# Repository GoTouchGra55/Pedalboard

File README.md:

# Multi-Effects Pedal Board

A custom multi-effects guitar pedal board combining several audio effects into one compact unit. Designed primarily as a learning project to explore analog audio circuits, signal processing, and embedded control systems (obv).

Also I needed effects pedals and those things are absurdly expensive ;')

---

## Features

- **Distortion & Overdrive** – From mild warmth to heavy saturation
- **Chorus** – Thickens and widens the sound
- **Tremolo** – Rhythmic volume modulation
- **Delay** – Adds echo and spatial depth

---

##  Signal Chain

Input -> Overdrive/Distortion -> Chorus -> Tremolo -> Delay -> Output

> _Note: Signal order can be adjusted depending on design preferences._

---

## Power Requirements

- **Input Voltage:** 9V DC (center-negative)
- **Power Supply:** Regulated recommended
- Includes onboard regulation and decoupling for noise reduction

---

## Hardware Overview

- Individual circuits for each effect
- Decoupling capacitors for stable operation

---

## I/O

- **Input Jack:** 1/4" mono
- **Output Jack:** 1/4" mono
- **DC Jack:** 9V input

---

## 3D View

---

## Routing

## BOM

| Component | Purpose | Qty | Total Cost (USD) | Distributor |
|---|---|---:|---:|---|
| Stomp Switch | Toggle each effect | 1 | 25.53 | Daraz Nepal |
| 50k Potentiometer | Used in circuit | 1 | 7.38 | Daraz Nepal |
| 20k Potentiometer | Used in circuit | 1 | 5.08 | Daraz Nepal |
| 2k Potentiometer | Used in circuit | 1 | 5.22 | Daraz Nepal |
| 10k Potentiometer | Used in circuit | 1 | 0.63 | Daraz Nepal |
| 100k Potentiometer | Used in circuit | 1 | 1.24 | Daraz Nepal |
| 500k Potentiometer | Used in circuit | 1 | 5.08 | Daraz Nepal |
| B100k Potentiometer | Used in circuit | 1 | 0.50 | Daraz Nepal |
| B500K Potentiometer | Used in circuit | 1 | 0.50 | Daraz Nepal |
| PCB | Houses all components | 1 | 8.20 | JLCPCB |
| DC Barrel Jack | Power input connector | 1 | 0.44 | Daraz Nepal |
| 1uF Capacitor | Charge storage/filtering | 1 | 0.88 | Daraz Nepal |
| 220nF Capacitor | Charge storage/filtering | 1 | 0.88 | Daraz Nepal |
| 100nF Capacitor | Charge storage/filtering | 1 | 1.82 | Daraz Nepal |
| Ceramic Capacitors Kit | Misc capacitor assortment | 1 | 7.91 | Daraz Nepal |
| Capacitor Kit | General purpose capacitors | 1 | 2.97 | Daraz Nepal |
| 2.2M Resistor | Current limiting | 1 | 0.66 | Daraz Nepal |
| Resistor Kit | General purpose resistors | 1 | 3.92 | Daraz Nepal |
| LDR | Tremolo light-dependent resistance | 1 | 2.27 | Daraz Nepal |
| LED | Status indication | 1 | 0.87 | Daraz Nepal |
| Voltage Regulator (7805) | Voltage regulation | 1 | 1.31 | Daraz Nepal |
| PT2399 IC | Delay/chorus processing IC | 1 | 2.36 | Daraz Nepal |
| LM555 Timer | PWM generation for tremolo | 1 | 2.00 | Daraz Nepal |
| NE5532 Op Amp | Chorus effect op amp | 1 | 1.78 | Daraz Nepal |
| TL072 | Gain/effects op amp | 1 | 1.69 | Daraz Nepal |
| Diode | One-way current flow | 1 | 0.40 | Daraz Nepal |
| Schottky Diode | Fast low-drop diode | 1 | 0.93 | Daraz Nepal |
| 1N4148 Diode | Signal diode | 1 | 0.27 | Daraz Nepal |
| 2N3904 Transistor | Signal filtering/amplification | 1 | 0.63 | Daraz Nepal |
| Guitar Jack Socket | Guitar/amp I/O connection | 2 | 2.07 | Daraz Nepal |

## Estimated Total Cost

**~$94.54 USD**

> Note: Prices may vary depending on shipping, stock availability, and quantity ordered.

---

## Suppliers

- Daraz Nepal
- JLCPCB

---

## Notes

- Passive component kits (capacitors/resistors) include multiple values and quantities.
- Potentiometer values may vary depending on the final pedal circuit tuning.
- PCB pricing is estimated from JLCPCB prototype manufacturing quotes.

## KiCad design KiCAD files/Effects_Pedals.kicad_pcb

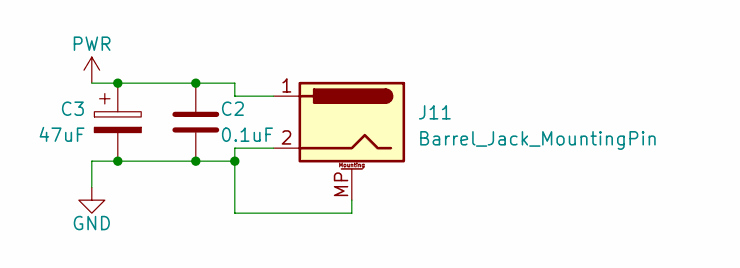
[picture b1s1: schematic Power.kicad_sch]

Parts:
C2: 0.1uF; C_Disc_D3.0mm_W2.0mm_P2.50mm
C3: 47uF; CP_Radial_D4.0mm_P1.50mm
J11: Barrel_Jack_MountingPin; BarrelJack_Horizontal

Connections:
GND: C2.2, C3.2, J11.2, J11.MP (MountPin); also elsewhere on the board
PWR: C2.1, C3.1, J11.1; also elsewhere on the board

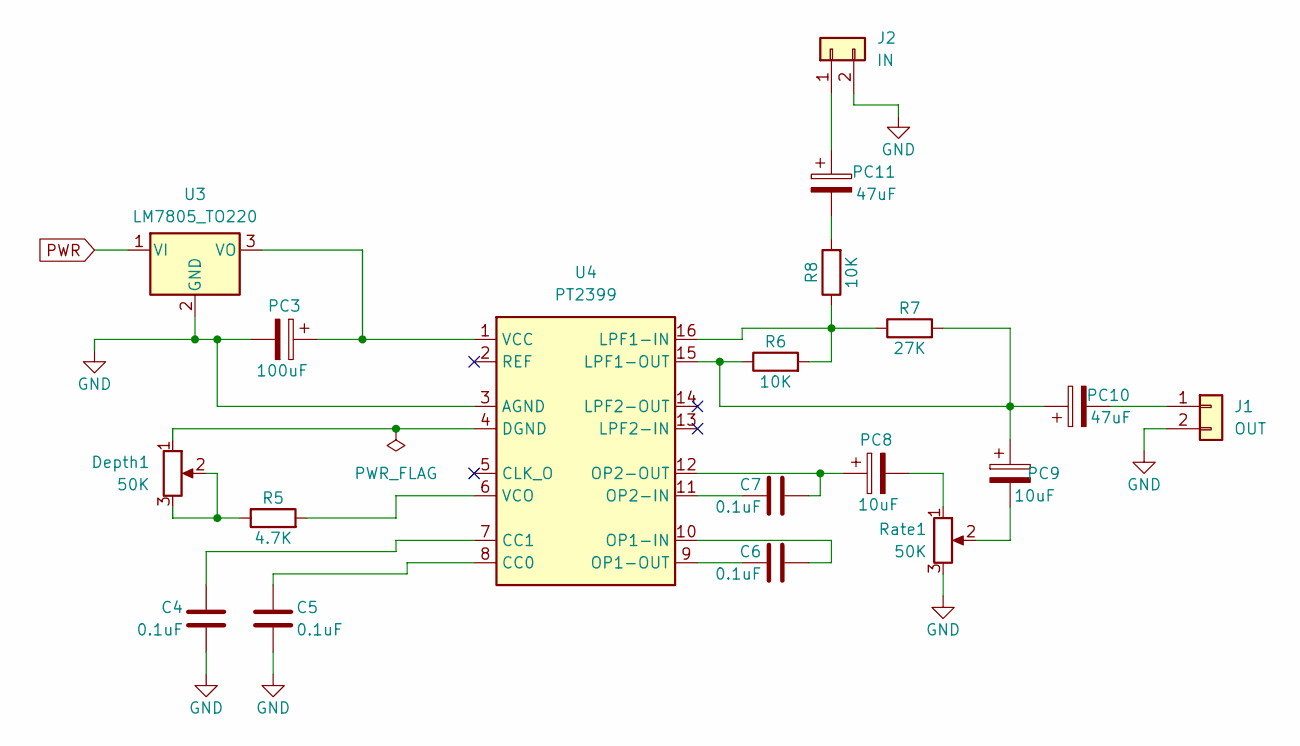
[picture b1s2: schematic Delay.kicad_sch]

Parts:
C4, C5, C6, C7: 0.1uF; C_Disc_D3.0mm_W2.0mm_P2.50mm
Depth1: 50K; PinSocket_1x03_P2.54mm_Vertical
J1: OUT; PinHeader_1x02_P1.00mm_Vertical
J2: IN; PinHeader_1x02_P1.00mm_Vertical
PC3: 100uF; CP_Radial_D4.0mm_P1.50mm
PC8, PC9: 10uF; CP_Radial_D4.0mm_P1.50mm
PC10, PC11: 47uF; CP_Radial_D4.0mm_P1.50mm
R5: 4.7K; R_Axial_DIN0207_L6.3mm_D2.5mm_P7.62mm_Horizontal
R6, R8: 10K; R_Axial_DIN0207_L6.3mm_D2.5mm_P7.62mm_Horizontal
R7: 27K; R_Axial_DIN0207_L6.3mm_D2.5mm_P7.62mm_Horizontal
Rate1: 50K; PinSocket_1x03_P2.54mm_Vertical
U3: LM7805_TO220; TO-220-3_Vertical
U4: PT2399; DIP-16_W7.62mm

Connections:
GND: C4.2, C5.2, J1.2, J2.2, PC3.2, Rate1.3, U3.2 (GND), U4.3 (AGND); also elsewhere on the board
unnamed: Depth1.2, Depth1.3, R5.1
unnamed: J1.1, PC10.2
unnamed: J2.1, PC11.1
unnamed: PC8.2, Rate1.1
unnamed: PC9.2, Rate1.2
unnamed: PC11.2, R8.2
unnamed: PC3.1, U3.3 (VO), U4.1 (VCC)
unnamed: C5.1, U4.8 (CC0)
unnamed: C4.1, U4.7 (CC1)
unnamed: Depth1.1, U4.4 (DGND)
unnamed: R6.2, R7.1, R8.1, U4.16 (LPF1-IN)
unnamed: PC9.1, PC10.1, R6.1, R7.2, U4.15 (LPF1-OUT)
unnamed: C6.2, U4.10 (OP1-IN)
unnamed: C6.1, U4.9 (OP1-OUT)
unnamed: C7.1, U4.11 (OP2-IN)
unnamed: C7.2, PC8.1, U4.12 (OP2-OUT)
unnamed: R5.2, U4.6 (VCO)
PWR: U3.1 (VI); also elsewhere on the board

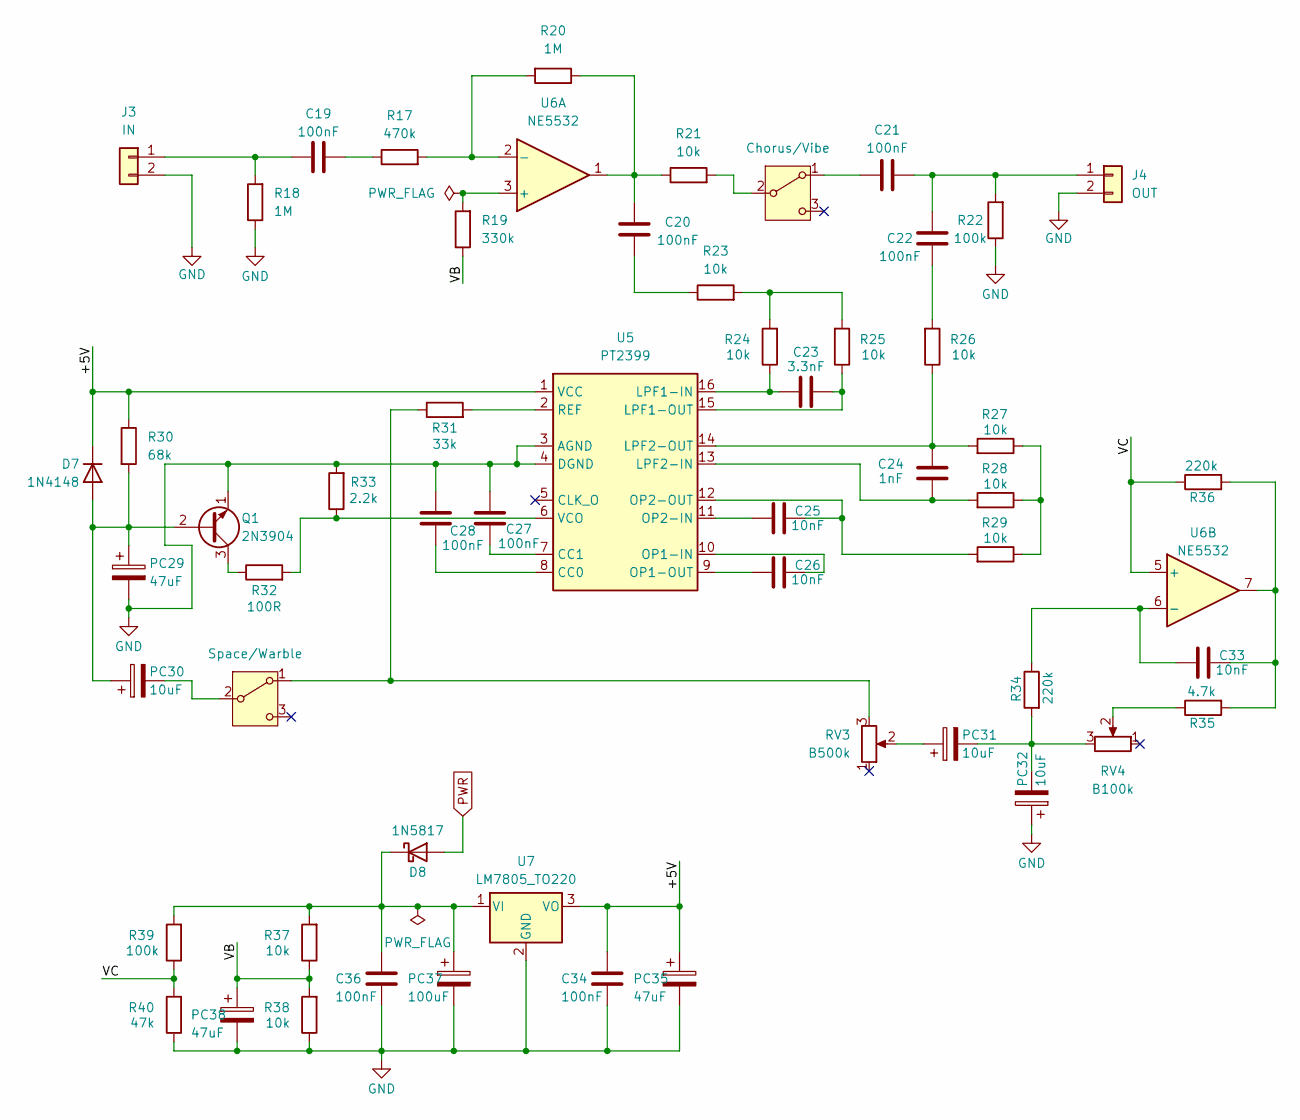
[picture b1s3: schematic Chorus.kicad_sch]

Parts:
C19, C20, C21, C22, C27, C28, C34, C36: 100nF; C_Disc_D3.0mm_W2.0mm_P2.50mm
C23: 3.3nF; C_Disc_D3.0mm_W2.0mm_P2.50mm
C24: 1nF; C_Disc_D3.0mm_W2.0mm_P2.50mm
C25, C26, C33: 10nF; C_Disc_D3.0mm_W2.0mm_P2.50mm
D7: 1N4148; D_DO-35_SOD27_P7.62mm_Horizontal
D8: 1N5817; D_DO-41_SOD81_P10.16mm_Horizontal
J3: IN; PinHeader_1x02_P1.00mm_Vertical
J4: OUT; PinHeader_1x02_P1.00mm_Vertical
PC29, PC35, PC38: 47uF; CP_Radial_D4.0mm_P1.50mm
PC30, PC31, PC32: 10uF; CP_Radial_D4.0mm_P1.50mm
PC37: 100uF; CP_Radial_D4.0mm_P1.50mm
Q1: 2N3904; TO-92_Inline
R17: 470k; R_Axial_DIN0207_L6.3mm_D2.5mm_P7.62mm_Horizontal
R18, R20: 1M; R_Axial_DIN0207_L6.3mm_D2.5mm_P7.62mm_Horizontal
R19: 330k; R_Axial_DIN0207_L6.3mm_D2.5mm_P7.62mm_Horizontal
R21, R23, R24, R25, R26, R27, R28, R29, R37, R38: 10k; R_Axial_DIN0207_L6.3mm_D2.5mm_P7.62mm_Horizontal
R22, R39: 100k; R_Axial_DIN0207_L6.3mm_D2.5mm_P7.62mm_Horizontal
R30: 68k; R_Axial_DIN0207_L6.3mm_D2.5mm_P7.62mm_Horizontal
R31: 33k; R_Axial_DIN0207_L6.3mm_D2.5mm_P7.62mm_Horizontal
R32: 100R; R_Axial_DIN0207_L6.3mm_D2.5mm_P7.62mm_Horizontal
R33: 2.2k; R_Axial_DIN0207_L6.3mm_D2.5mm_P7.62mm_Horizontal
R34, R36: 220k; R_Axial_DIN0207_L6.3mm_D2.5mm_P7.62mm_Horizontal
R35: 4.7k; R_Axial_DIN0207_L6.3mm_D2.5mm_P7.62mm_Horizontal
R40: 47k; R_Axial_DIN0207_L6.3mm_D2.5mm_P7.62mm_Horizontal
RV3: B500k; PinSocket_1x03_P2.54mm_Vertical
RV4: B100k; PinSocket_1x03_P2.54mm_Vertical
SW1: Chorus/Vibe; PinSocket_1x03_P2.54mm_Vertical
SW3: Space/Warble; PinSocket_1x03_P2.54mm_Vertical
U5: PT2399; DIP-16_W7.62mm
U6: NE5532; DIP-8_W7.62mm
U7: LM7805_TO220; TO-220-3_Vertical

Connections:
/Chorus/+5V: C34.1, D7.1 (K), PC35.1, R30.1, U5.1 (VCC), U7.3 (VO)
/Chorus/VB: PC38.1, R19.1, R37.1, R38.2
/Chorus/VC: R36.1, R39.1, R40.2, U6.5 (+)
GND: C27.1, C28.1, C34.2, C36.2, J3.2, J4.2, PC29.2, PC32.1, PC35.2, PC37.2, PC38.2, Q1.1 (E), R18.1, R22.1, R33.2, R38.1, R40.1, U5.3 (AGND), U5.4 (DGND), U7.2 (GND); also elsewhere on the board
unnamed: C19.2, R17.1
unnamed: C20.1, R23.1
unnamed: C20.2, R20.1, R21.1, U6.1
unnamed: C22.2, R26.2
unnamed: C33.1, R35.2, R36.2, U6.7
unnamed: D7.2 (A), PC29.1, PC30.1, Q1.2 (B), R30.2
unnamed: C36.1, D8.1 (K), PC37.1, R37.2, R39.2, U7.1 (VI)
unnamed: C19.1, J3.1, R18.2
unnamed: C21.1, C22.1, J4.1, R22.2
unnamed: PC31.1, RV3.2
unnamed: PC31.2, PC32.2, R34.2, RV4.3
unnamed: Q1.3 (C), R32.1
unnamed: R23.2, R24.2, R25.2
unnamed: R27.1, R28.1, R29.1
unnamed: R35.1, RV4.2
unnamed: C21.2, SW1.1 (A)
unnamed: R21.2, SW1.2 (B)
unnamed: R31.1, RV3.3, SW3.1 (A)
unnamed: PC30.2, SW3.2 (B)
unnamed: C28.2, U5.8 (CC0)
unnamed: C27.2, U5.7 (CC1)
unnamed: C23.2, R24.1, U5.16 (LPF1-IN)
unnamed: C23.1, R25.1, U5.15 (LPF1-OUT)
unnamed: C24.2, R28.2, U5.13 (LPF2-IN)
unnamed: C24.1, R26.1, R27.2, U5.14 (LPF2-OUT)
unnamed: C26.1, U5.10 (OP1-IN)
unnamed: C26.2, U5.9 (OP1-OUT)
unnamed: C25.2, U5.11 (OP2-IN)
unnamed: C25.1, R29.2, U5.12 (OP2-OUT)
unnamed: R31.2, U5.2 (REF)
unnamed: R32.2, R33.1, U5.6 (VCO)
unnamed: R19.2, U6.3 (+)
unnamed: R17.2, R20.2, U6.2 (-)
unnamed: C33.2, R34.1, U6.6 (-)
PWR: D8.2 (A); also elsewhere on the board

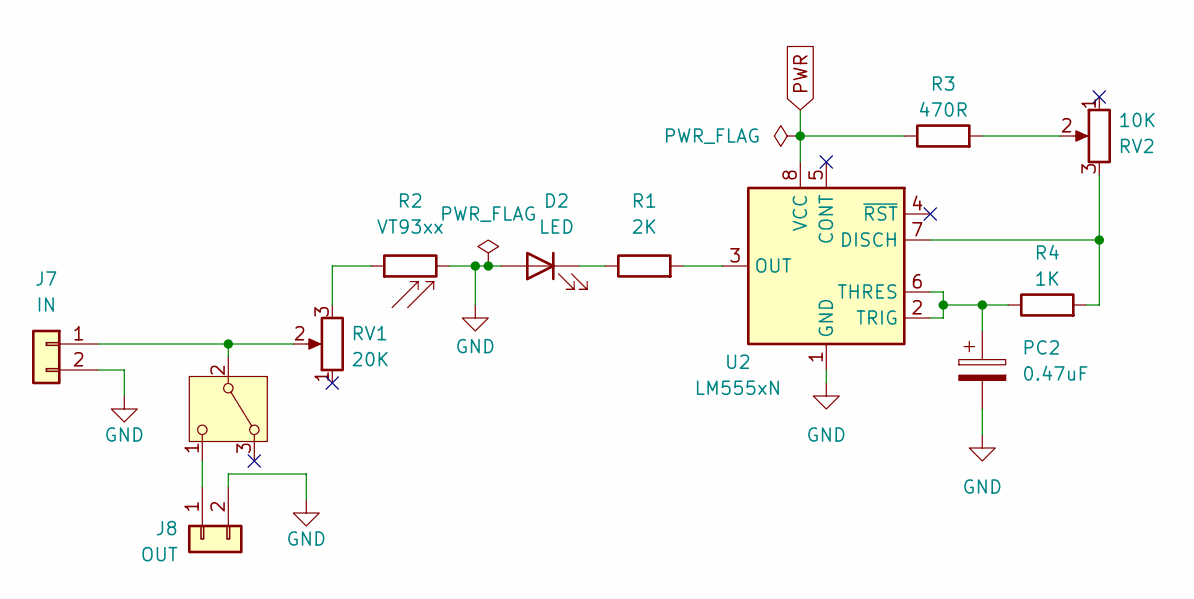
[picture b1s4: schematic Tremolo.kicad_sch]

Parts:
D2: LED; LED_D5.0mm
J7: IN; PinHeader_1x02_P1.00mm_Vertical
J8: OUT; PinHeader_1x02_P1.00mm_Vertical
PC2: 0.47uF; CP_Radial_D4.0mm_P1.50mm
R1: 2K; R_Axial_DIN0207_L6.3mm_D2.5mm_P7.62mm_Horizontal
R2: VT93xx; R_LDR_4.9x4.2mm_P2.54mm_Vertical
R3: 470R; R_Axial_DIN0207_L6.3mm_D2.5mm_P7.62mm_Horizontal
R4: 1K; R_Axial_DIN0207_L6.3mm_D2.5mm_P7.62mm_Horizontal
RV1: 20K; PinSocket_1x03_P2.54mm_Vertical
RV2: 10K; PinSocket_1x03_P2.54mm_Vertical
SW2: SW_Nidec_CAS-120A1; PinSocket_1x02_P2.54mm_Vertical
U2: LM555xN; DIP-8_W7.62mm

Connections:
GND: D2.2 (A), J7.2, J8.2, PC2.2, R2.2, U2.1 (GND); also elsewhere on the board
unnamed: D2.1 (K), R1.1
unnamed: J7.1, RV1.2, SW2.2 (B)
unnamed: J8.1, SW2.1 (C)
unnamed: R2.1, RV1.3
unnamed: R3.2, RV2.2
unnamed: R4.2, RV2.3, U2.7 (DISCH)
unnamed: R1.2, U2.3 (OUT)
unnamed: PC2.1, R4.1, U2.2 (TRIG), U2.6 (THRES)
PWR: R3.1, U2.8 (VCC); also elsewhere on the board

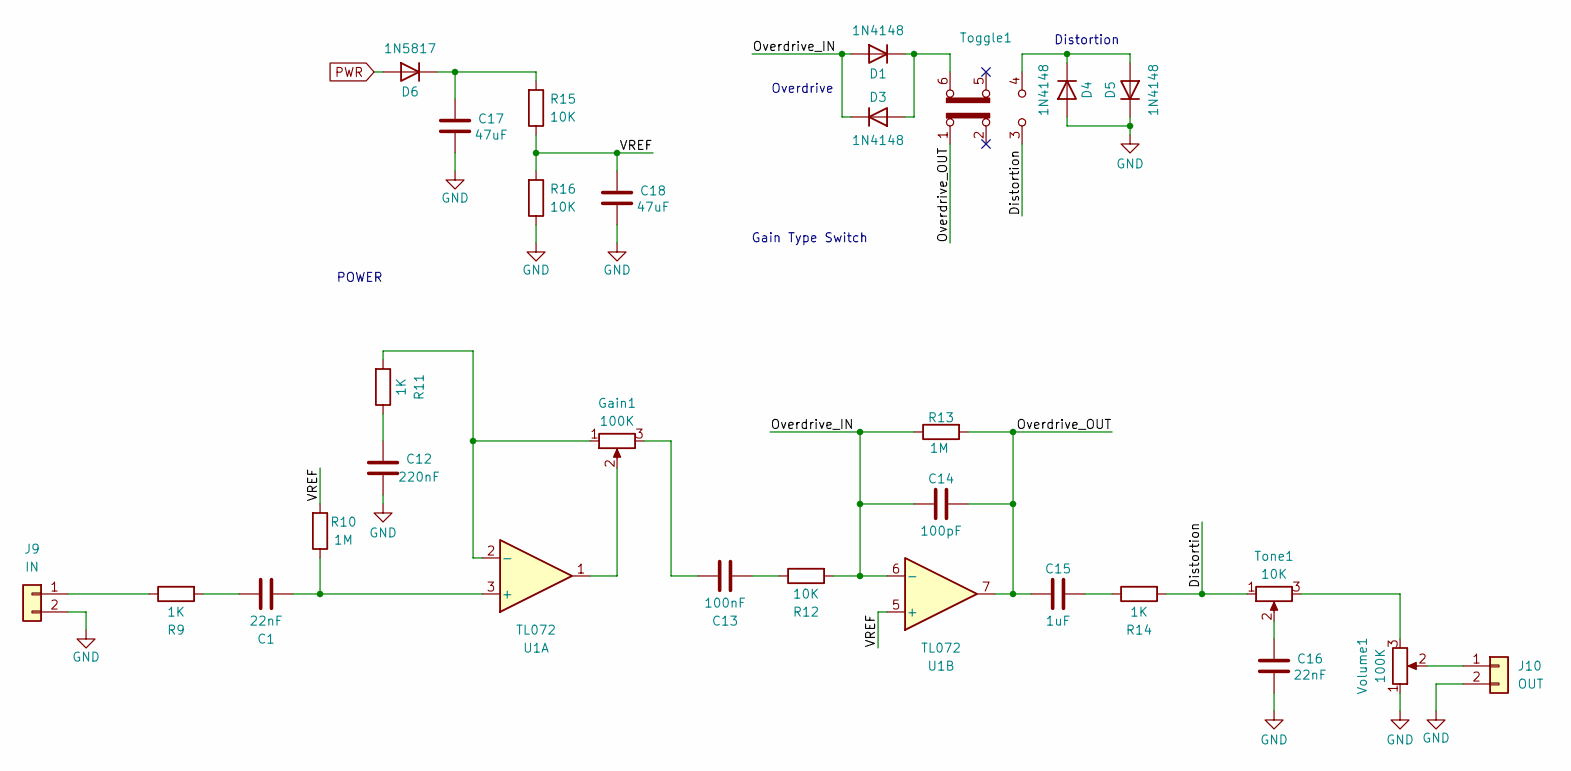
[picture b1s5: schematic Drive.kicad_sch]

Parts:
C1, C16: 22nF; C_Disc_D3.0mm_W2.0mm_P2.50mm
C12: 220nF; C_Disc_D3.0mm_W2.0mm_P2.50mm
C13: 100nF; C_Disc_D3.0mm_W2.0mm_P2.50mm
C14: 100pF; C_Disc_D3.0mm_W2.0mm_P2.50mm
C15: 1uF; C_Disc_D3.0mm_W2.0mm_P2.50mm
C17, C18: 47uF; C_Disc_D3.0mm_W2.0mm_P2.50mm
D1, D3, D4, D5: 1N4148; D_DO-35_SOD27_P7.62mm_Horizontal
D6: 1N5817; D_DO-41_SOD81_P10.16mm_Horizontal
Gain1: 100K; PinSocket_1x03_P2.54mm_Vertical
J9: IN; PinHeader_1x02_P1.00mm_Vertical
J10: OUT; PinHeader_1x02_P1.00mm_Vertical
R9, R11, R14: 1K; R_Axial_DIN0207_L6.3mm_D2.5mm_P7.62mm_Horizontal
R10, R13: 1M; R_Axial_DIN0207_L6.3mm_D2.5mm_P7.62mm_Horizontal
R12, R15, R16: 10K; R_Axial_DIN0207_L6.3mm_D2.5mm_P7.62mm_Horizontal
Toggle1: SW_Slide_DPDT; PinSocket_1x03_P2.54mm_Vertical
Tone1: 10K; PinSocket_1x03_P2.54mm_Vertical
U1: TL072; DIP-8_W7.62mm
Volume1: 100K; PinSocket_1x03_P2.54mm_Vertical

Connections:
/OD_Dist/Distortion: R14.2, Toggle1.3 (C), Tone1.1
/OD_Dist/Overdrive_IN: C14.2, D1.2 (A), D3.1 (K), R12.2, R13.1, U1.6 (-)
/OD_Dist/Overdrive_OUT: C14.1, C15.2, R13.2, Toggle1.1 (A), U1.7
/OD_Dist/VREF: C18.1, R10.2, R15.1, R16.2, U1.5 (+)
GND: C12.2, C16.2, C17.2, C18.2, D4.2 (A), D5.1 (K), J9.2, J10.2, R16.1, Volume1.1; also elsewhere on the board
unnamed: C1.2, R9.2
unnamed: C12.1, R11.1
unnamed: C13.1, R12.1
unnamed: C13.2, Gain1.3
unnamed: C15.1, R14.1
unnamed: C16.1, Tone1.2
unnamed: D1.1 (K), D3.2 (A), Toggle1.6 (C)
unnamed: D4.1 (K), D5.2 (A), Toggle1.4 (A)
unnamed: C17.1, D6.1 (K), R15.2
unnamed: Gain1.2, U1.1
unnamed: J9.1, R9.1
unnamed: J10.1, Volume1.2
unnamed: Tone1.3, Volume1.3
unnamed: C1.1, R10.1, U1.3 (+)
unnamed: Gain1.1, R11.2, U1.2 (-)
PWR: D6.2 (A); also elsewhere on the board

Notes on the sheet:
Distortion
Gain Type Switch
POWER
Overdrive

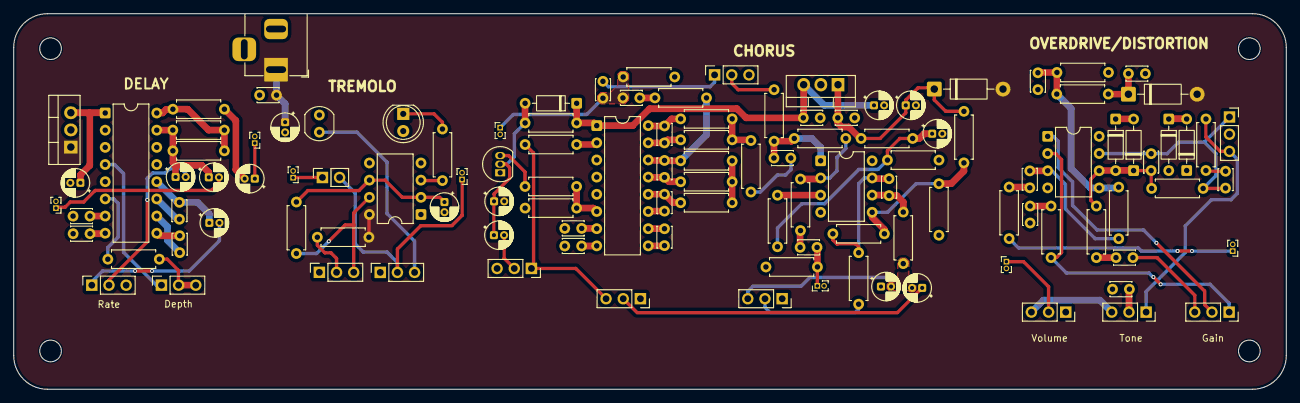
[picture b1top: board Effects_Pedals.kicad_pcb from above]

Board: 2 copper layers, 188.2 x 55.5 mm, 118 parts (0 on the bottom side), 83 nets.

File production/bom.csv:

Designator,Footprint,Quantity,Value,LCSC Part #
"C1, C16",C_Disc_D3.0mm_W2.0mm_P2.50mm,2,22nF,
C12,C_Disc_D3.0mm_W2.0mm_P2.50mm,1,220nF,
"C13, C19, C20, C21, C22, C27, C28, C34, C36",C_Disc_D3.0mm_W2.0mm_P2.50mm,9,100nF,
C14,C_Disc_D3.0mm_W2.0mm_P2.50mm,1,100pF,
C15,C_Disc_D3.0mm_W2.0mm_P2.50mm,1,1uF,
"C17, C18",C_Disc_D3.0mm_W2.0mm_P2.50mm,2,47uF,
"C2, C4, C5, C6, C7",C_Disc_D3.0mm_W2.0mm_P2.50mm,5,0.1uF,
C23,C_Disc_D3.0mm_W2.0mm_P2.50mm,1,3.3nF,
C24,C_Disc_D3.0mm_W2.0mm_P2.50mm,1,1nF,
"C25, C26, C33",C_Disc_D3.0mm_W2.0mm_P2.50mm,3,10nF,
"C3, PC10, PC11, PC29, PC35, PC38",CP_Radial_D4.0mm_P1.50mm,6,47uF,
"D1, D3, D4, D5, D7",D_DO-35_SOD27_P7.62mm_Horizontal,5,1N4148,
D2,LED_D5.0mm,1,LED,
"D6, D8",D_DO-41_SOD81_P10.16mm_Horizontal,2,1N5817,
"DEPTH1, RATE1",PinSocket_1x03_P2.54mm_Vertical,2,50K,
"GAIN1, VOLUME1",PinSocket_1x03_P2.54mm_Vertical,2,100K,
"J1, J10, J4, J8",PinHeader_1x02_P1.00mm_Vertical,4,OUT,
J11,BarrelJack_Horizontal,1,Barrel_Jack_MountingPin,
"J2, J3, J7, J9",PinHeader_1x02_P1.00mm_Vertical,4,IN,
PC2,CP_Radial_D4.0mm_P1.50mm,1,0.47uF,
"PC3, PC37",CP_Radial_D4.0mm_P1.50mm,2,100uF,
"PC30, PC31, PC32, PC8, PC9",CP_Radial_D4.0mm_P1.50mm,5,10uF,
Q1,TO-92_Inline,1,2N3904,
R1,R_Axial_DIN0207_L6.3mm_D2.5mm_P7.62mm_Horizontal,1,2K,
"R10, R13, R18, R20",R_Axial_DIN0207_L6.3mm_D2.5mm_P7.62mm_Horizontal,4,1M,
"R11, R14, R4, R9",R_Axial_DIN0207_L6.3mm_D2.5mm_P7.62mm_Horizontal,4,1K,
"R12, R15, R16, R21, R23, R24, R25, R26, R27, R28, R29, R37, R38, R6, R8",R_Axial_DIN0207_L6.3mm_D2.5mm_P7.62mm_Horizontal,15,10K,
R17,R_Axial_DIN0207_L6.3mm_D2.5mm_P7.62mm_Horizontal,1,470k,
R19,R_Axial_DIN0207_L6.3mm_D2.5mm_P7.62mm_Horizontal,1,330k,
R2,R_LDR_4.9x4.2mm_P2.54mm_Vertical,1,VT93xx,
"R22, R39",R_Axial_DIN0207_L6.3mm_D2.5mm_P7.62mm_Horizontal,2,100k,
R3,R_Axial_DIN0207_L6.3mm_D2.5mm_P7.62mm_Horizontal,1,470R,
R30,R_Axial_DIN0207_L6.3mm_D2.5mm_P7.62mm_Horizontal,1,68k,
R31,R_Axial_DIN0207_L6.3mm_D2.5mm_P7.62mm_Horizontal,1,33k,
R32,R_Axial_DIN0207_L6.3mm_D2.5mm_P7.62mm_Horizontal,1,100R,
R33,R_Axial_DIN0207_L6.3mm_D2.5mm_P7.62mm_Horizontal,1,2.2k,
"R34, R36",R_Axial_DIN0207_L6.3mm_D2.5mm_P7.62mm_Horizontal,2,220k,
"R35, R5",R_Axial_DIN0207_L6.3mm_D2.5mm_P7.62mm_Horizontal,2,4.7k,
R40,R_Axial_DIN0207_L6.3mm_D2.5mm_P7.62mm_Horizontal,1,47k,
R7,R_Axial_DIN0207_L6.3mm_D2.5mm_P7.62mm_Horizontal,1,27K,
RV1,PinSocket_1x03_P2.54mm_Vertical,1,20K,
"RV2, TONE1",PinSocket_1x03_P2.54mm_Vertical,2,10K,
RV3,PinSocket_1x03_P2.54mm_Vertical,1,B500k,
RV4,PinSocket_1x03_P2.54mm_Vertical,1,B100k,
SW1,PinSocket_1x03_P2.54mm_Vertical,1,Chorus/Vibe,
SW2,PinSocket_1x02_P2.54mm_Vertical,1,SW_Nidec_CAS-120A1,
SW3,PinSocket_1x03_P2.54mm_Vertical,1,Space/Warble,
TOGGLE1,PinSocket_1x03_P2.54mm_Vertical,1,SW_Slide_DPDT,
U1,DIP-8_W7.62mm,1,TL072,
U2,DIP-8_W7.62mm,1,LM555xN,
"U3, U7",TO-220-3_Vertical,2,LM7805_TO220,
"U4, U5",DIP-16_W7.62mm,2,PT2399,
U6,DIP-8_W7.62mm,1,NE5532,

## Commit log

2026-04-14 Add files
2026-04-15 Add new files
2026-05-07 Add bom and update readme
